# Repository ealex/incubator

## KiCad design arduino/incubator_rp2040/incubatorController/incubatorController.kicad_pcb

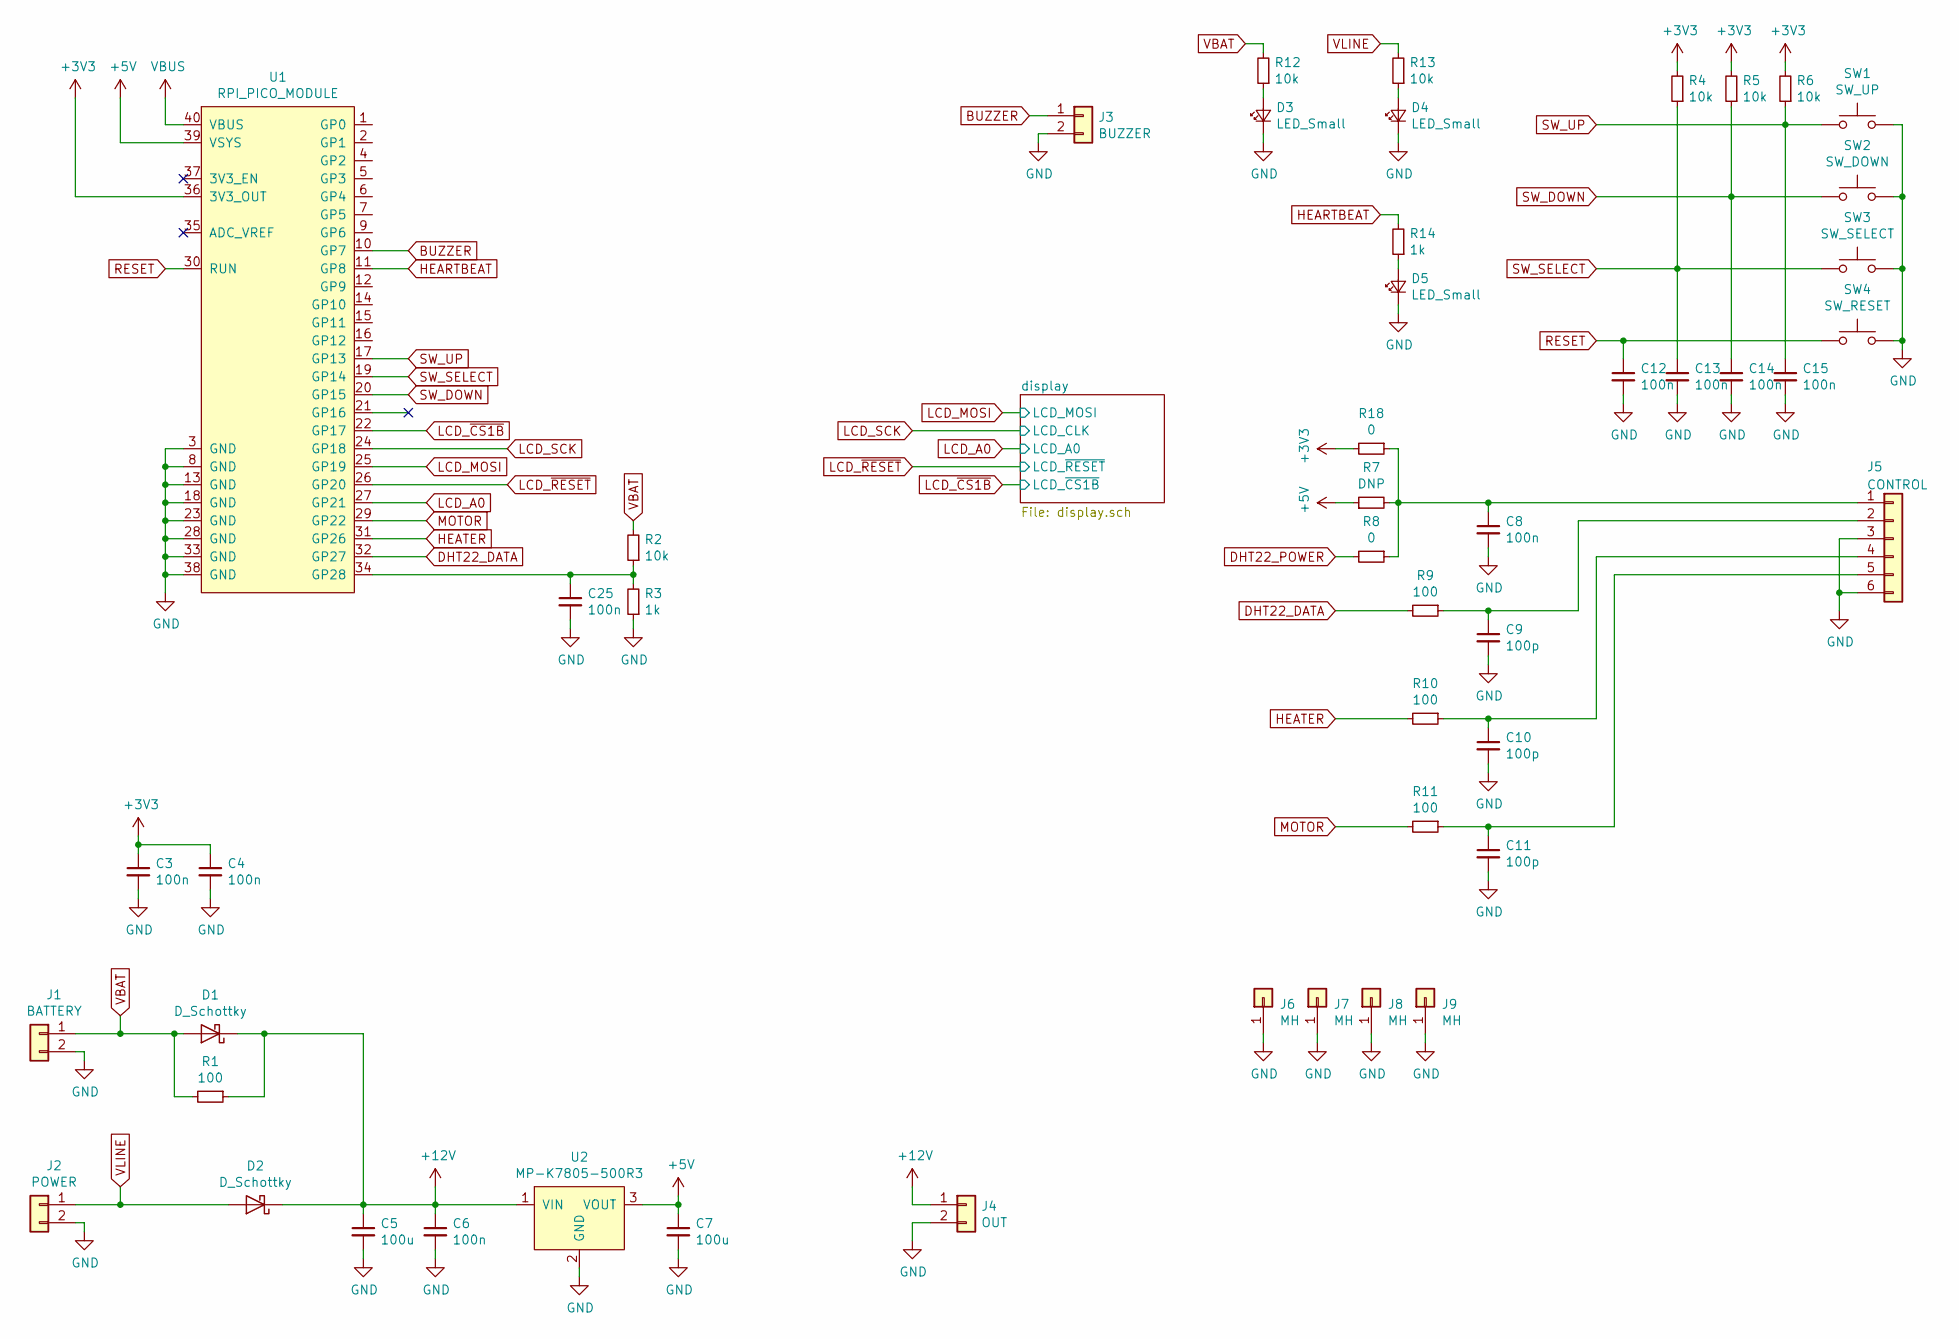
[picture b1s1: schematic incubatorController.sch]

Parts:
C3, C4, C6, C8, C12, C13, C14, C15, C25: 100n; C_1206_3216Metric
C5, C7: 100u; CP_Radial_D10.0mm_P5.00mm
C9, C10, C11: 100p; C_1206_3216Metric
D1, D2: D_Schottky; D_SMA-SMB_Universal_Handsoldering
D3, D4, D5: LED_Small; LED_0805_2012Metric
J1: BATTERY; 691213510002
J2: POWER; 691213510002
J3: BUZZER; PinHeader_1x02_P2.54mm_Vertical
J4: OUT; 691213510002
J5: CONTROL; MP008516
J6, J7, J8, J9: MH; MountingHole_3.2mm_M3_DIN965
R1: 100; PinHeader_1x02_P2.54mm_Vertical
R2, R4, R5, R6, R12, R13: 10k; R_1206_3216Metric
R3, R14: 1k; R_1206_3216Metric
R7: DNP; R_1206_3216Metric
R8, R18: 0; R_1206_3216Metric
R9, R10, R11: 100; R_1206_3216Metric
SW1: SW_UP; EVPASCB1A
SW2: SW_DOWN; EVPASCB1A
SW3: SW_SELECT; EVPASCB1A
SW4: SW_RESET; SW_SPST_B3U-1000P
U1: RPI_PICO_MODULE; RPi_Pico_SMD_TH
U2: MP-K7805-500R3

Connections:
+3V3: C3.1, C4.1, R4.2, R5.2, R6.2, R18.2, U1.36 (3V3_OUT); also elsewhere on the board
+5V: C7.1, R7.1, U1.39 (VSYS), U2.3 (VOUT)
+12V: C5.1, C6.1, D1.1 (K), D2.1 (K), J4.1, R1.1, U2.1 (VIN)
BUZZER: J3.1, U1.10 (GP7)
DHT22_DATA: R9.2, U1.32 (GP27)
GND: C3.2, C4.2, C5.2, C6.2, C7.2, C8.2, C9.2, C10.2, C11.2, C12.2, C13.2, C14.2, C15.2, C25.2, D3.1 (K), D4.1 (K), D5.1 (K), J1.2, J2.2, J3.2, J4.2, J5.3, J5.6, J6.1, J7.1, J8.1, J9.1, R3.1, SW1.2, SW2.2, SW3.2, SW4.2, U1.3 (GND), U1.8 (GND), U1.13 (GND), U1.18 (GND), U1.23 (GND), U1.28 (GND), U1.33 (GND), U1.38 (GND), U2.2 (GND); also elsewhere on the board
HEARTBEAT: R14.2, U1.11 (GP8)
HEATER: R10.2, U1.31 (GP26)
LCD_A0: U1.27 (GP21); also elsewhere on the board
LCD_MOSI: U1.25 (GP19); also elsewhere on the board
LCD_SCK: U1.24 (GP18); also elsewhere on the board
LCD_~CS1B: U1.22 (GP17); also elsewhere on the board
LCD_~RESET: U1.26 (GP20); also elsewhere on the board
MOTOR: R11.2, U1.29 (GP22)
unnamed: C8.1, J5.1, R7.2, R8.1, R18.1
unnamed: C9.1, J5.2, R9.1
unnamed: C10.1, J5.4, R10.1
unnamed: C11.1, J5.5, R11.1
unnamed: C25.1, R2.1, R3.2, U1.34 (GP28)
unnamed: D3.2 (A), R12.1
unnamed: D4.2 (A), R13.1
unnamed: D5.2 (A), R14.1
RESET: C12.1, SW4.1, U1.30 (RUN)
SW_DOWN: C14.1, R5.1, SW2.1, U1.20 (GP15)
SW_SELECT: C13.1, R4.1, SW3.1, U1.19 (GP14)
SW_UP: C15.1, R6.1, SW1.1, U1.17 (GP13)
VBAT: D1.2 (A), J1.1, R1.2, R2.2, R12.2
VLINE: D2.2 (A), J2.1, R13.2

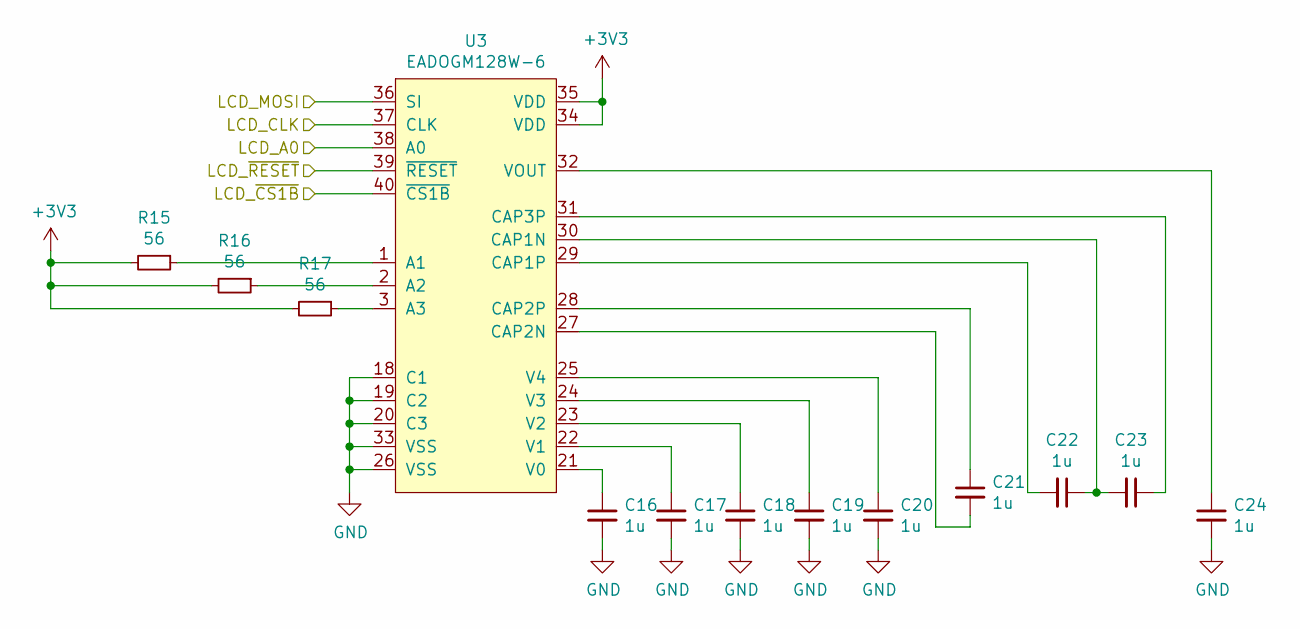
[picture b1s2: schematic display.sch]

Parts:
C16, C17, C18, C19, C20, C21, C22, C23, C24: 1u; C_0805_2012Metric
R15, R16, R17: 56; R_1206_3216Metric
U3: EADOGM128W-6; EADOGM128

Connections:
+3V3: R15.2, R16.2, R17.2, U3.34 (VDD), U3.35 (VDD); also elsewhere on the board
GND: C16.2, C17.2, C18.2, C19.2, C20.2, C24.2, U3.18 (C1), U3.19 (C2), U3.20 (C3), U3.26 (VSS), U3.33 (VSS); also elsewhere on the board
LCD_A0: U3.38 (A0); also elsewhere on the board
LCD_MOSI: U3.36 (SI); also elsewhere on the board
LCD_SCK: U3.37 (CLK); also elsewhere on the board
LCD_~CS1B: U3.40 (~CS1B); also elsewhere on the board
LCD_~RESET: U3.39 (~RESET); also elsewhere on the board
unnamed: C16.1, U3.21 (V0)
unnamed: C17.1, U3.22 (V1)
unnamed: C18.1, U3.23 (V2)
unnamed: C19.1, U3.24 (V3)
unnamed: C20.1, U3.25 (V4)
unnamed: C21.1, U3.28 (CAP2P)
unnamed: C21.2, U3.27 (CAP2N)
unnamed: C22.1, C23.2, U3.30 (CAP1N)
unnamed: C22.2, U3.29 (CAP1P)
unnamed: C23.1, U3.31 (CAP3P)
unnamed: C24.1, U3.32 (VOUT)
unnamed: R15.1, U3.1 (A1)
unnamed: R16.1, U3.2 (A2)
unnamed: R17.1, U3.3 (A3)

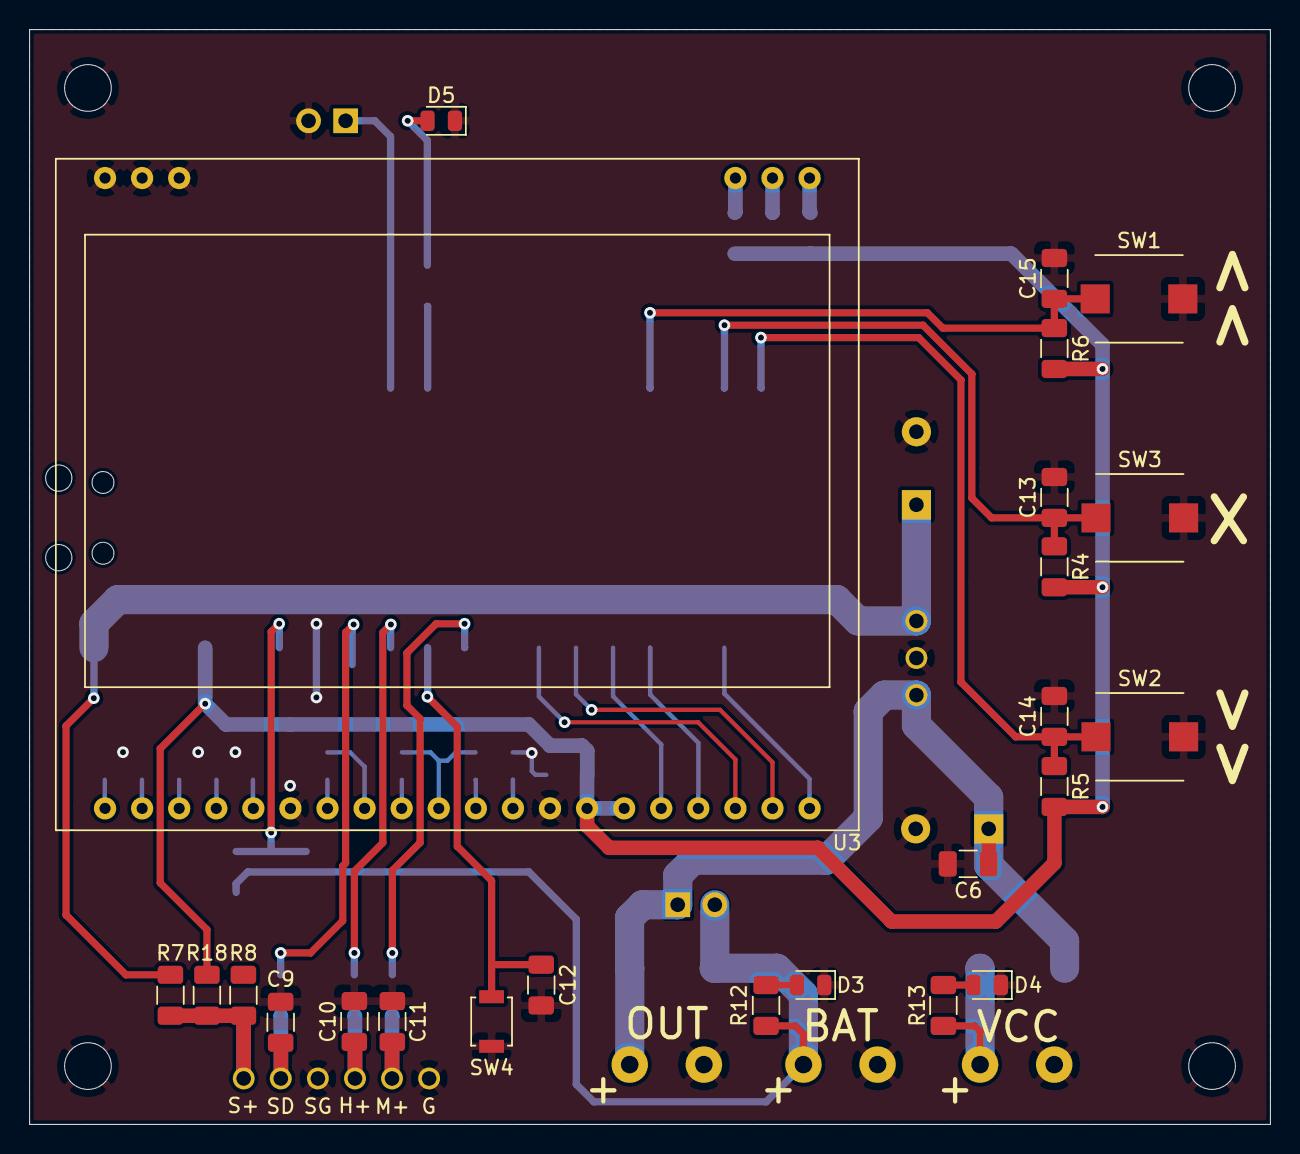
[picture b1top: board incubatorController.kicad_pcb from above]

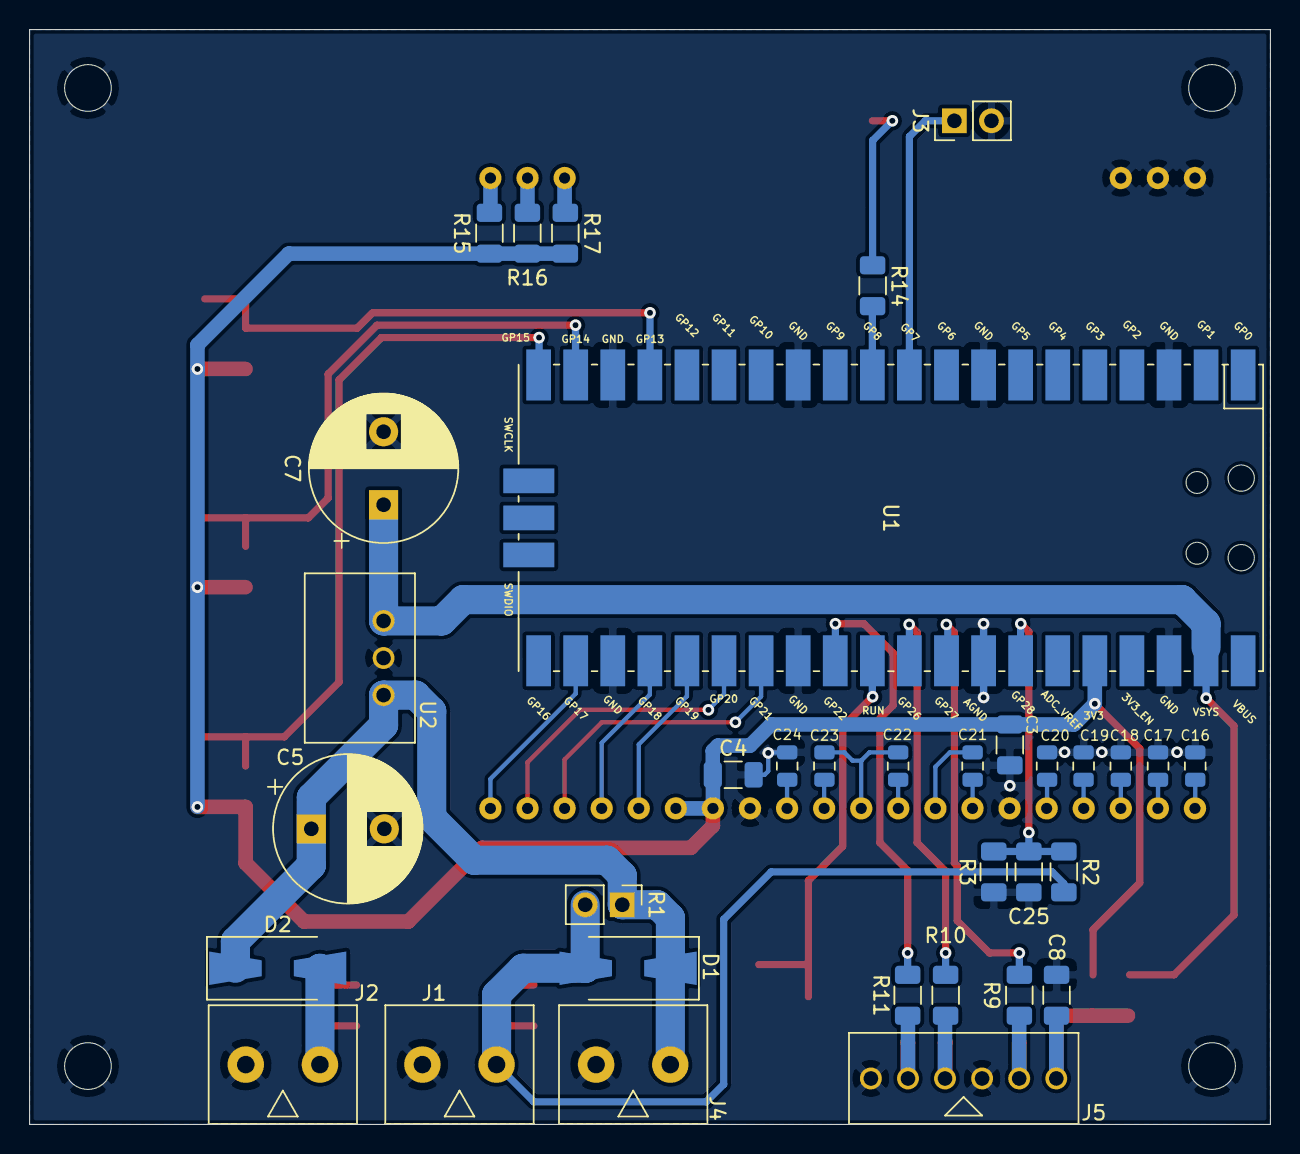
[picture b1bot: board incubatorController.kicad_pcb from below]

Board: 2 copper layers, 85.0 x 75.0 mm, 62 parts (34 on the bottom side), 42 nets.

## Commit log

2022-03-03 control firmware
2022-03-09 version that can keep temperature
2022-03-09 add frame and prepare for linkage gears
2022-03-10 update CAD and break down UI in different tasks
2022-03-20 update code
2022-03-22 update CAD
2022-04-26 update motor end plates and motor to cilinder connection
2022-05-02 update egg turner system
2022-05-03 start controller v2
2022-05-09 add rpi pico based schematic
2022-05-15 port to FreeRTOS multi-core, and the new hardware
